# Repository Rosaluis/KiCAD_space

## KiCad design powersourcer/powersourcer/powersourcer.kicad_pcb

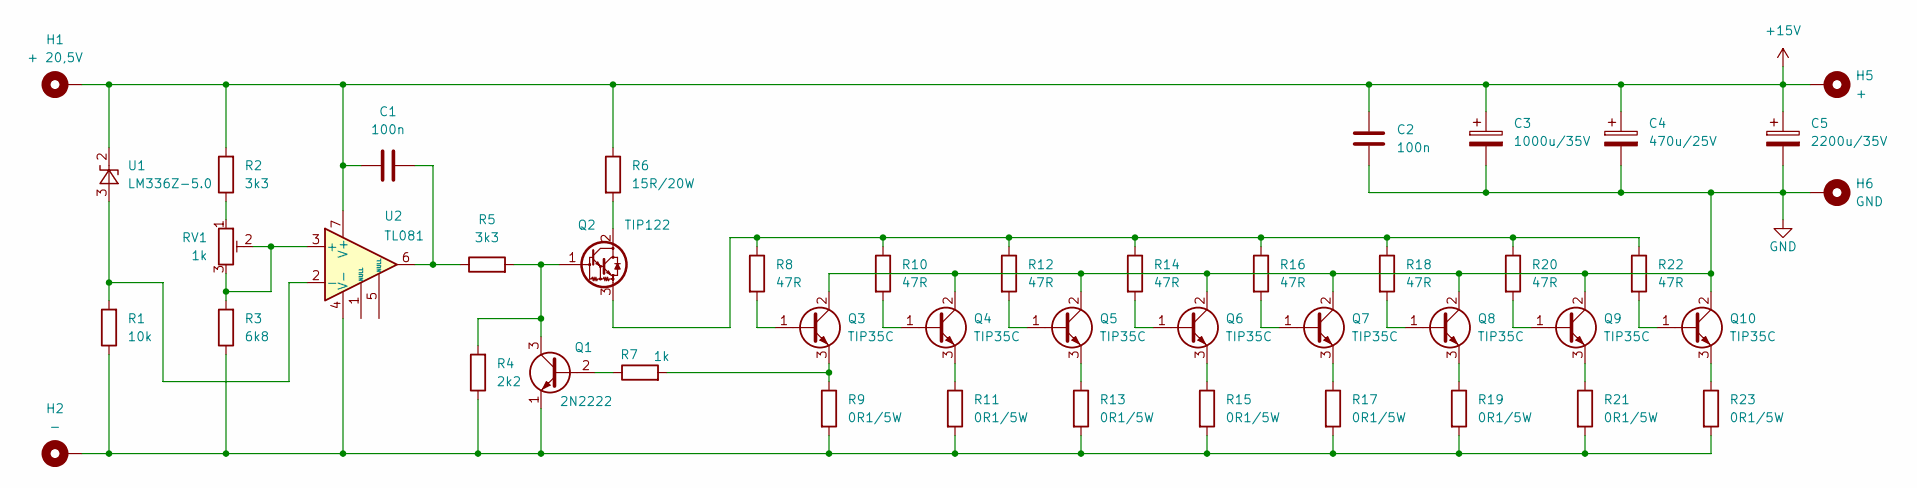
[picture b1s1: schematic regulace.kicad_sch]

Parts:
C1, C2: 100n; C_1206_3216Metric_Pad1.33x1.80mm_HandSolder
C3: 1000u/35V; CP_Radial_D22.0mm_P10.00mm_SnapIn
C4: 470u/25V; CP_Radial_D10.0mm_P5.00mm
C5: 2200u/35V; CP_Radial_D22.0mm_P10.00mm_SnapIn
H1: + 20,5V; PinHeader_1x01_P1.00mm_Vertical
H2: -; PinHeader_1x01_P1.00mm_Vertical
H5: +; PinHeader_1x01_P1.00mm_Vertical
H6: GND; PinHeader_1x01_P1.00mm_Vertical
Q1: 2N2222; TO-39-3
Q2: TIP122; TO-247-3_Vertical
Q3, Q4, Q5, Q6, Q7, Q8, Q9, Q10: TIP35C; TO-247-3_Horizontal_TabUp
R1: 10k; R_1206_3216Metric_Pad1.30x1.75mm_HandSolder
R2, R5: 3k3; R_1206_3216Metric_Pad1.30x1.75mm_HandSolder
R3: 6k8; R_1206_3216Metric_Pad1.30x1.75mm_HandSolder
R4: 2k2; R_1206_3216Metric_Pad1.30x1.75mm_HandSolder
R6: 15R/20W; R_Radial_Power_L13.0mm_W9.0mm_P5.00mm
R7: 1k; R_1206_3216Metric_Pad1.30x1.75mm_HandSolder
R8, R10, R12, R14, R16, R18, R20, R22: 47R; R_Axial_DIN0309_L9.0mm_D3.2mm_P12.70mm_Horizontal
R9, R11, R13, R15, R17, R19, R21, R23: 0R1/5W; R_Radial_Power_L13.0mm_W9.0mm_P5.00mm
RV1: 1k; Potentiometer_Bourns_3296W_Vertical
U1: LM336Z-5.0; TO-92_Inline
U2: TL081; DIP-8_W7.62mm

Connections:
+15V: C1.1, C2.1, C3.1, C4.1, C5.1, H1.1 (1_1), H5.1 (1_1), R2.2, R6.1, U1.2 (K), U2.7 (V+)
GND: C2.2, C3.2, C4.2, C5.2, H6.1 (1_1), Q3.2 (C), Q4.2 (C), Q5.2 (C), Q6.2 (C), Q7.2 (C), Q8.2 (C), Q9.2 (C), Q10.2 (C)
unnamed: C1.2, R5.1, U2.6
unnamed: Q1.2 (B), R7.1
unnamed: Q1.3 (C), Q2.1 (B), R4.2, R5.2
unnamed: H2.1 (1_1), Q1.1 (E), R1.1, R3.1, R4.1, R9.2, R11.2, R13.2, R15.2, R17.2, R19.2, R21.2, R23.2, U2.4 (V-)
unnamed: Q2.2 (C), R6.2
unnamed: Q2.3 (E), R8.1, R10.1, R12.1, R14.1, R16.1, R18.1, R20.1, R22.1
unnamed: Q3.1 (B), R8.2
unnamed: Q3.3 (E), R7.2, R9.1
unnamed: Q4.1 (B), R10.2
unnamed: Q4.3 (E), R11.1
unnamed: Q5.1 (B), R12.2
unnamed: Q5.3 (E), R13.1
unnamed: Q6.1 (B), R14.2
unnamed: Q6.3 (E), R15.1
unnamed: Q7.1 (B), R16.2
unnamed: Q7.3 (E), R17.1
unnamed: Q8.1 (B), R18.2
unnamed: Q8.3 (E), R19.1
unnamed: Q9.1 (B), R20.2
unnamed: Q9.3 (E), R21.1
unnamed: Q10.1 (B), R22.2
unnamed: Q10.3 (E), R23.1
unnamed: R2.1, RV1.1
unnamed: R1.2, U1.3 (A), U2.2 (-)
unnamed: R3.2, RV1.2, RV1.3, U2.3 (+)

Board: 2 copper layers, 45 parts (8 on the bottom side), 27 nets, no tracks yet.

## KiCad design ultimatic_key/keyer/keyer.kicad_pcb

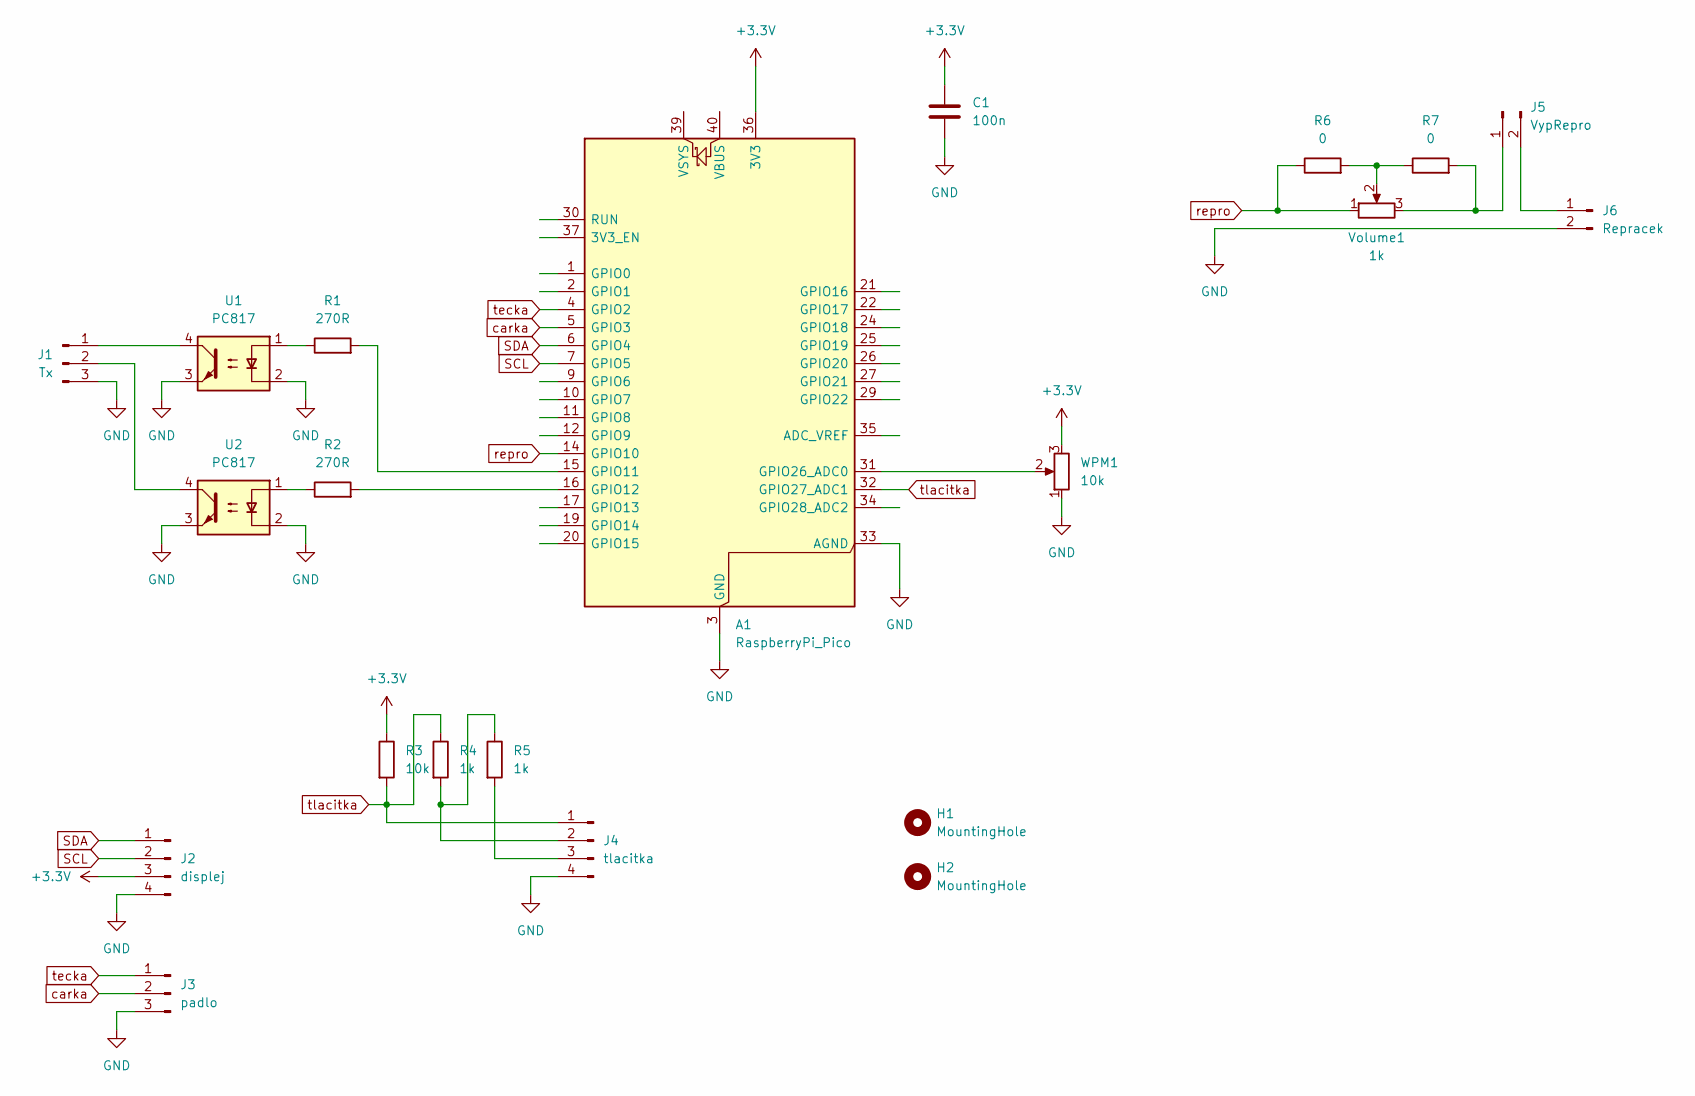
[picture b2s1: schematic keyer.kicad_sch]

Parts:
A1: RaspberryPi_Pico; RaspberryPi_Pico_Common_THT
C1: 100n; C_1206_3216Metric_Pad1.33x1.80mm_HandSolder
H1, H2: MountingHole; MountingHole_3.2mm_M3_DIN965_Pad
J1: Tx; PinHeader_1x03_P2.54mm_Vertical
J2: displej; PinHeader_1x04_P2.54mm_Vertical
J3: padlo; PinHeader_1x03_P2.54mm_Vertical
J4: tlacitka; PinHeader_1x04_P2.54mm_Vertical
J5: VypRepro; PinHeader_1x02_P2.54mm_Vertical
J6: Repracek; PinHeader_1x02_P2.54mm_Vertical
R1, R2: 270R; R_1206_3216Metric_Pad1.30x1.75mm_HandSolder
R3: 10k; R_1206_3216Metric_Pad1.30x1.75mm_HandSolder
R4, R5: 1k; R_1206_3216Metric_Pad1.30x1.75mm_HandSolder
R6, R7: 0; R_1206_3216Metric_Pad1.30x1.75mm_HandSolder
U1, U2: PC817; SOP-4_7.5x4.1mm_P2.54mm_PC817
Volume1: 1k; Potentiometer_Piher_T-16H_Single_Horizontal
WPM1: 10k; Potentiometer_Piher_T-16H_Single_Horizontal

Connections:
+3.3V: A1.36 (3V3), C1.1, J2.3, R3.1, WPM1.3
GND: A1.3 (GND), A1.8 (GND), A1.13 (GND), A1.18 (GND), A1.23 (GND), A1.28 (GND), A1.33 (AGND), A1.38 (GND), C1.2, J1.3, J2.4, J3.3, J4.4, J6.2, U1.2, U1.3, U2.2, U2.3, WPM1.1
unnamed: A1.15 (GPIO11), R1.2
unnamed: A1.16 (GPIO12), R2.2
unnamed: A1.31 (GPIO26_ADC0), WPM1.2
unnamed: J1.1, U1.4
unnamed: J1.2, U2.4
unnamed: J4.2, R4.2, R5.1
unnamed: J4.3, R5.2
unnamed: J5.1, R7.2, Volume1.3
unnamed: J5.2, J6.1
unnamed: R1.1, U1.1
unnamed: R2.1, U2.1
unnamed: R6.2, R7.1, Volume1.2
SCL: A1.7 (GPIO5), J2.2
SDA: A1.6 (GPIO4), J2.1
carka: A1.5 (GPIO3), J3.2
repro: A1.14 (GPIO10), R6.1, Volume1.1
tecka: A1.4 (GPIO2), J3.1
tlacitka: A1.32 (GPIO27_ADC1), J4.1, R3.2, R4.1

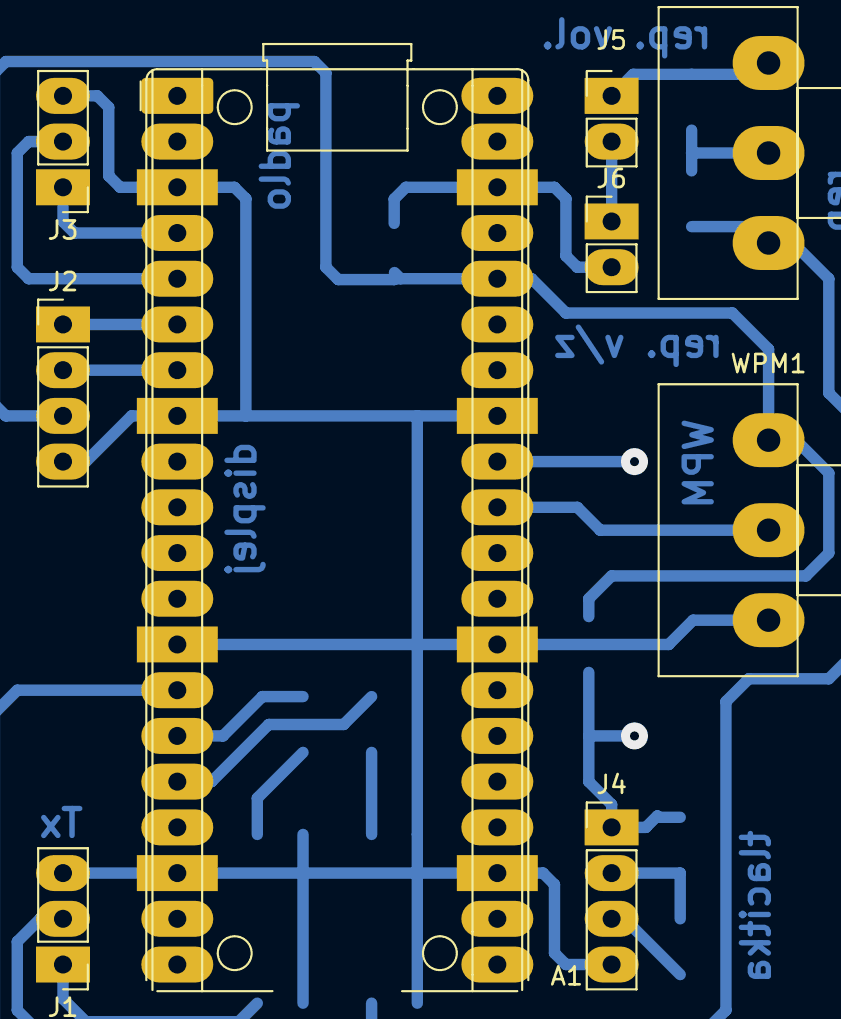
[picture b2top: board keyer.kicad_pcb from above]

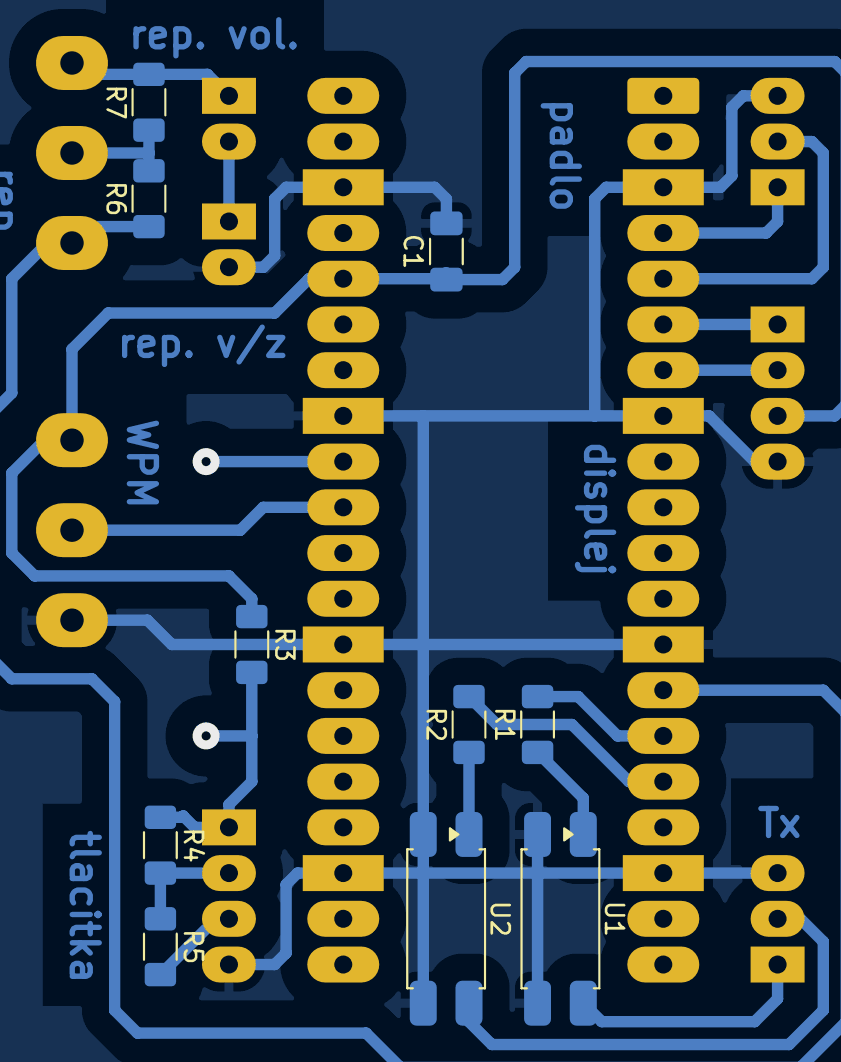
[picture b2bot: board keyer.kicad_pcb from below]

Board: 2 copper layers, 19 parts (10 on the bottom side), 20 nets.

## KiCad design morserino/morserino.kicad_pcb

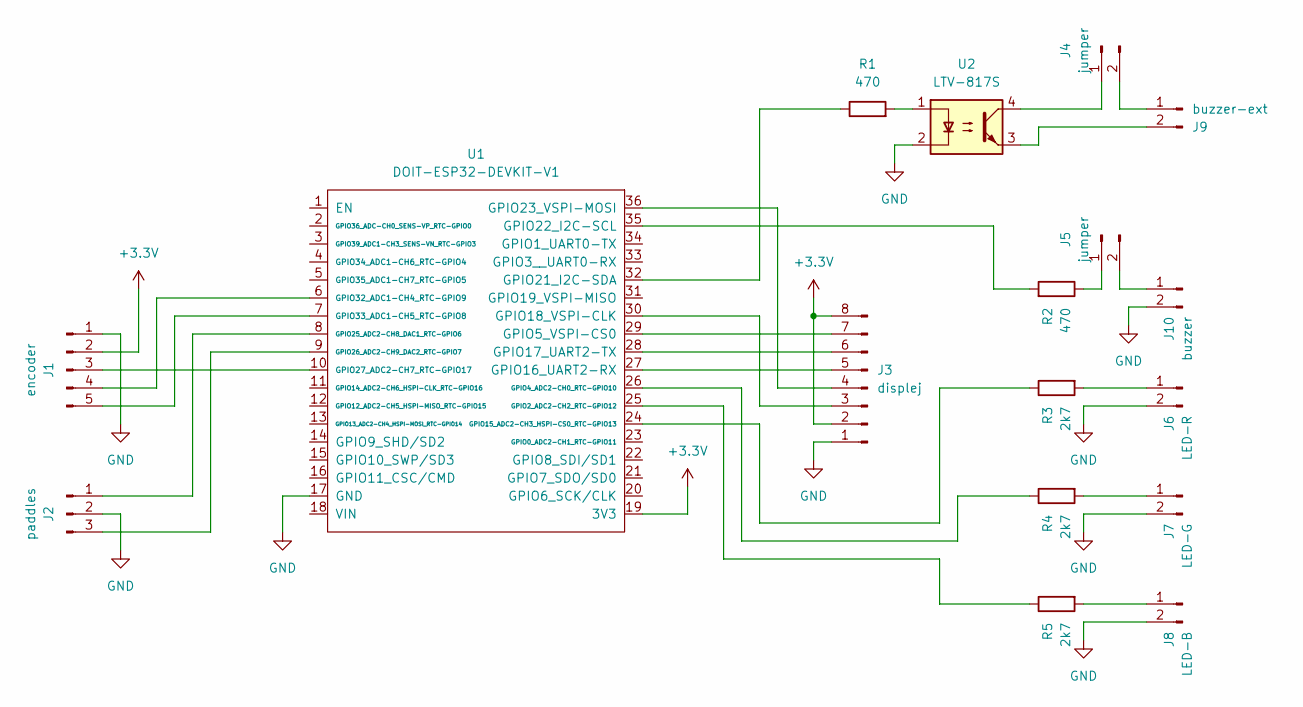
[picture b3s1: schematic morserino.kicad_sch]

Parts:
J1: encoder; PinHeader_1x05_P2.54mm_Vertical_big_pads
J2: paddles; PinHeader_1x03_P2.54mm_Vertical_big_pads
J3: displej; PinHeader_1x08_P2.54mm_Vertical_big_pads
J4, J5: jumper; PinSocket_1x02_P2.54mm_Vertical_big_pads
J6: LED-R; PinSocket_1x02_P2.54mm_Vertical_big_pads
J7: LED-G; PinSocket_1x02_P2.54mm_Vertical_big_pads
J8: LED-B; PinSocket_1x02_P2.54mm_Vertical_big_pads
J9: buzzer-ext; PinSocket_1x02_P2.54mm_Vertical_big_pads
J10: buzzer; PinSocket_1x02_P2.54mm_Vertical_big_pads
R1, R2: 470; R_1206_3216Metric_Pad1.30x1.75mm_HandSolder
R3, R4, R5: 2k7; R_1206_3216Metric_Pad1.30x1.75mm_HandSolder
U1: DOIT-ESP32-DEVKIT-V1; ESP32-DOIT-DEVKIT_big_pads
U2: LTV-817S; SMDIP-4_W9.53mm

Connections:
+3.3V: J1.2, J3.2, J3.8, U1.19 (3V3)
GND: J1.1, J2.2, J3.1, J6.2, J7.2, J8.2, J10.2, U1.17 (GND), U2.2
unnamed: J1.3, U1.10 (GPIO27_ADC2-CH7_RTC-GPIO17)
unnamed: J1.4, U1.6 (GPIO32_ADC1-CH4_RTC-GPIO9)
unnamed: J1.5, U1.7 (GPIO33_ADC1-CH5_RTC-GPIO8)
unnamed: J2.1, U1.8 (GPIO25_ADC2-CH8_DAC1_RTC-GPIO6)
unnamed: J2.3, U1.9 (GPIO26_ADC2-CH9_DAC2_RTC-GPIO7)
unnamed: J3.3, U1.30 (GPIO18_VSPI-CLK)
unnamed: J3.4, U1.36 (GPIO23_VSPI-MOSI)
unnamed: J3.5, U1.27 (GPIO16_UART2-RX)
unnamed: J3.6, U1.28 (GPIO17_UART2-TX)
unnamed: J3.7, U1.29 (GPIO5_VSPI-CS0)
unnamed: J4.1, U2.4
unnamed: J4.2, J9.1
unnamed: J5.1, R2.1
unnamed: J6.1, R3.2
unnamed: J7.1, R4.2
unnamed: J8.1, R5.2
unnamed: J9.2, U2.3
unnamed: J5.2, J10.1
unnamed: R1.2, U2.1
unnamed: R5.1, U1.25 (GPIO2_ADC2-CH2_RTC-GPIO12)
unnamed: R4.1, U1.26 (GPIO4_ADC2-CH0_RTC-GPIO10)
unnamed: R3.1, U1.24 (GPIO15_ADC2-CH3_HSPI-CS0_RTC-GPIO13)
unnamed: R1.1, U1.32 (GPIO21_I2C-SDA)
unnamed: R2.2, U1.35 (GPIO22_I2C-SCL)

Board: 2 copper layers, 17 parts (6 on the bottom side), 26 nets, no tracks yet.

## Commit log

2026-02-19 Schema je hotove - doma překontrolovat podle breadboardu.
2026-02-19 První návrh PCB.
2026-04-22 Zdroj - spouštění.
2026-04-23 zdroj.
2026-04-24 poslední práce.
2026-04-29 Přidány bázové odpory.
2026-04-29 Knihovna patic.
2026-04-29 Upravené knihovny - velikost plošek.
2026-04-29 7W odpor.
2026-04-29 pouzdro CP a chladič.
2026-04-29 Revert "Merge branch 'knihovny' of https://github.com/Rosaluis/KiCAD_space into zdroj"
    This reverts commit 3ae39fce54fcdbf34580f56dbf586aeb6a5abba3, reversing
    changes made to 21906c4974e3bbb210b8702f33b781dc4735bac2.
2026-04-29 Osvitová UV lampa na PCB.
2026-04-30 Přidány kontakty pro externí start tlačítko.
2026-04-30 Reapply "Merge branch 'knihovny' of https://github.com/Rosaluis/KiCAD_space into zdroj"
    This reverts commit 2f14b997a4806e9ac11dec1cfc80ef4eb8ad11c2.
2026-04-30 Další pouzdra.
2026-04-30 Patice potenciometru, svorek.
2026-04-30 update.
2026-04-30 jen bckups po otevření projektu.
2026-04-30 Save local changes
2026-04-30 změny.
2026-04-30 Celý se to posralo kvůli chybějícímu řádku.
2026-04-30 rozdýchávání knihovny, ale šlo to.
2026-05-07 Pouzdro na ležáka pro silové tranzistory.
2026-05-07 V práci otevřený projekt.
2026-05-07 V práci otevřený KiCAD.
2026-05-21 Doplněny bázové odpory silových tranzistorů.
2026-05-21 Přečíslování součástek před přiřazením pouzder.
2026-05-21 Přiřazení pouzder.
2026-05-21 TO-247-3-chladič nahoru.
2026-05-21 Jednodířková průchozí ploška, veliká.
2026-05-21 nevím kurva proč je to tady
2026-05-22 Práce na pcb. Odstraněny plošky pro externí resistor.
